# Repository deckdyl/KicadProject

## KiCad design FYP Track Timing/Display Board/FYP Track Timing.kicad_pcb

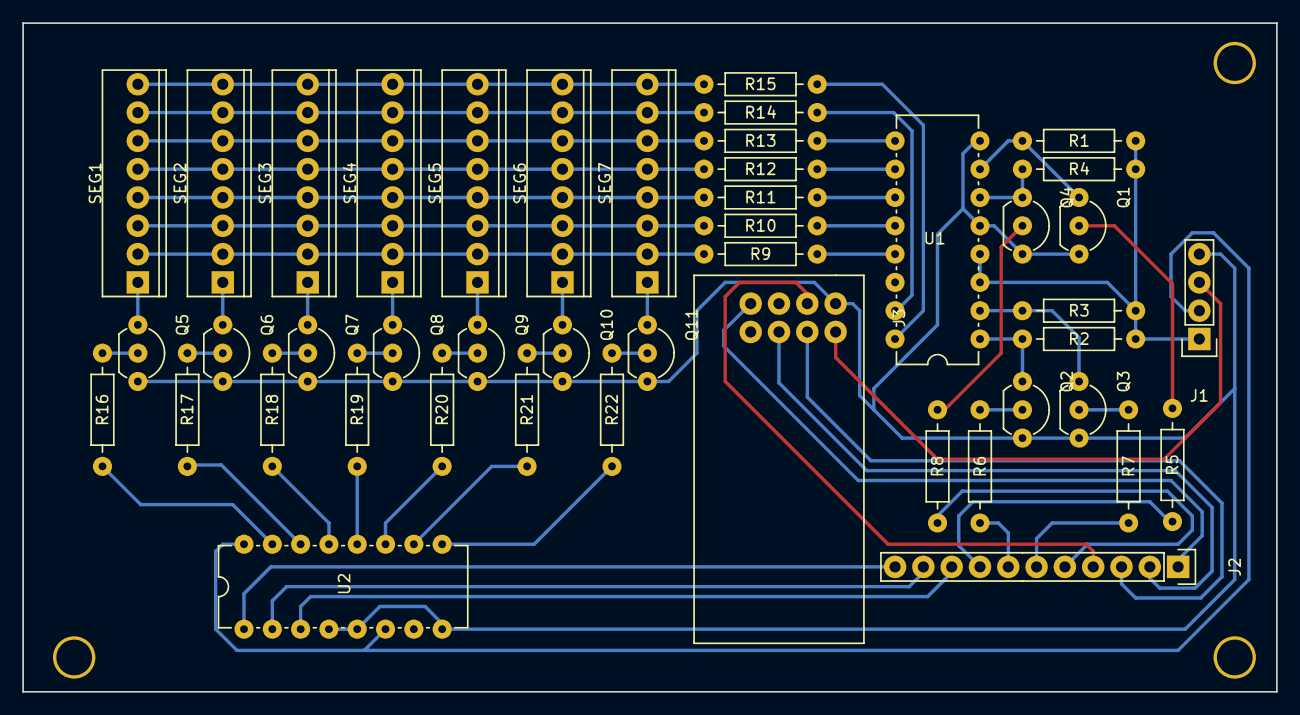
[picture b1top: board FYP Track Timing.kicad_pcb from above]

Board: 2 copper layers, 112.5 x 60.0 mm, 45 parts (0 on the bottom side), 58 nets.

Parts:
J1: Power; Pin_Header_Straight_1x04
J2: I/O; Pin_Header_Straight_1x11
J3: NRF24L01
Q1, Q2, Q3, Q4, Q5, Q6, Q7, Q8, Q9, Q10, Q11: 2N3904; TO-92_Inline_Wide
R1, R2, R3, R4: 10kΩ; Resistor-0.25W
R5, R6, R7, R8: 1kΩ; Resistor-0.25W
R9, R10, R11, R12, R13, R14, R15: 180Ω; Resistor-0.25W
R16, R17, R18, R19, R20, R21, R22: 470Ω; Resistor-0.25W
SEG1, SEG2, SEG3, SEG4, SEG5, SEG6, SEG7: KYX-30101AS; MolexHeader-7seg
U1: 4511; IC_PDIP_16pin
U2: 74HC238; IC_PDIP_16pin

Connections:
+3V3: J1.3, J3.2
+5V: J1.2, U2.6, U2.16
+9V: J1.1, R1.1, R2.1, R3.1, R4.1, U1.3, U1.4
GND: J1.4, J3.1, Q1.3, Q2.3, Q3.3, Q4.3, Q5.3, Q6.3, Q7.3, Q8.3, Q9.3, Q10.3, Q11.3, U1.5, U1.8, U2.4, U2.5, U2.8
unnamed: Q1.1, R1.2, U1.7
unnamed: Q1.2, R5.2
unnamed: Q2.1, R2.2, U1.1
unnamed: Q2.2, R6.2
unnamed: Q3.1, R3.2, U1.2
unnamed: Q3.2, R7.2
unnamed: Q4.1, R4.2, U1.6
unnamed: Q4.2, R8.2
unnamed: Q5.1, SEG1.1,5
unnamed: Q5.2, R16.2
unnamed: Q6.1, SEG2.1,5
unnamed: Q6.2, R17.2
unnamed: Q7.1, SEG3.1,5
unnamed: Q7.2, R18.2
unnamed: Q8.1, SEG4.1,5
unnamed: Q8.2, R19.2
unnamed: Q9.1, SEG5.1,5
unnamed: Q9.2, R20.2
unnamed: Q10.1, SEG6.1,5
unnamed: Q10.2, R21.2
unnamed: Q11.1, SEG7.1,5
unnamed: Q11.2, R22.2
unnamed: R9.1, U1.13
unnamed: R9.2, SEG1.7, SEG2.7, SEG3.7, SEG4.7, SEG5.7, SEG6.7, SEG7.7
unnamed: R10.1, U1.12
unnamed: R10.2, SEG1.6, SEG2.6, SEG3.6, SEG4.6, SEG5.6, SEG6.6, SEG7.6
unnamed: R11.1, U1.11
unnamed: R11.2, SEG1.4, SEG2.4, SEG3.4, SEG4.4, SEG5.4, SEG6.4, SEG7.4
unnamed: R12.1, U1.10
unnamed: R12.2, SEG1.3, SEG2.3, SEG3.3, SEG4.3, SEG5.3, SEG6.3, SEG7.3
unnamed: R13.1, U1.9
unnamed: R13.2, SEG1.2, SEG2.2, SEG3.2, SEG4.2, SEG5.2, SEG6.2, SEG7.2
unnamed: R14.1, U1.15
unnamed: R14.2, SEG1.9, SEG2.9, SEG3.9, SEG4.9, SEG5.9, SEG6.9, SEG7.9
unnamed: R15.1, U1.16
unnamed: R15.2, SEG1.10, SEG2.10, SEG3.10, SEG4.10, SEG5.10, SEG6.10, SEG7.10
unnamed: R16.1, U2.15
unnamed: R17.1, U2.14
unnamed: R18.1, U2.13
unnamed: R19.1, U2.12
unnamed: R20.1, U2.11
unnamed: R21.1, U2.10
unnamed: R22.1, U2.9
PinD2: J2.11, U2.1
PinD3: J2.10, U2.2
PinD4: J2.9, U2.3
PinD5: J2.8, R5.1
PinD6: J2.7, R6.1
PinD7: J2.6, R7.1
PinD8: J2.5, R8.1
PinD9: J2.4, J3.3
PinD10: J2.3, J3.4
PinD11: J2.2, J3.6
PinD12: J2.1, J3.7

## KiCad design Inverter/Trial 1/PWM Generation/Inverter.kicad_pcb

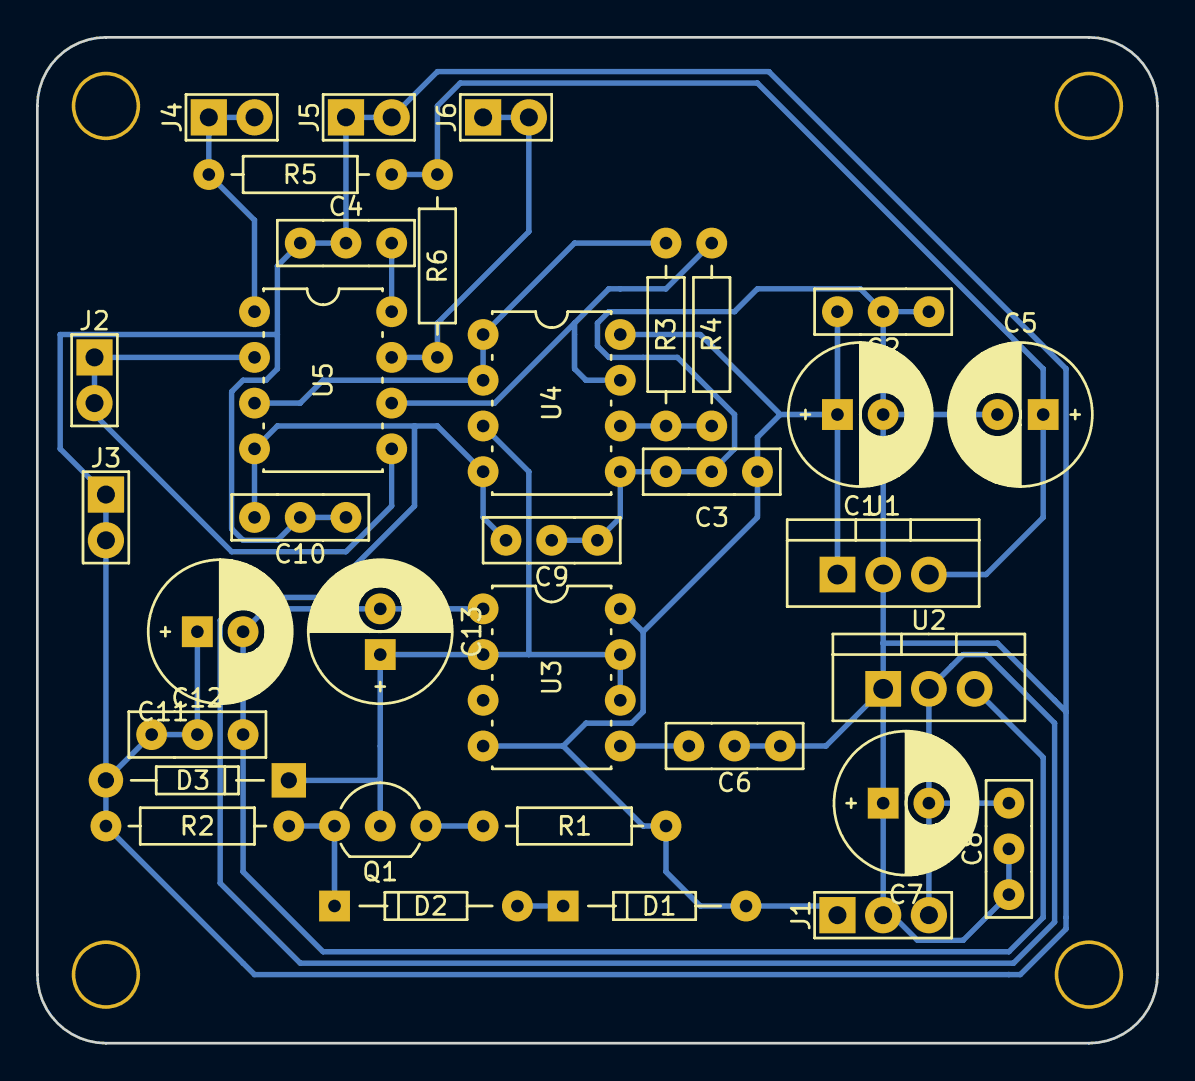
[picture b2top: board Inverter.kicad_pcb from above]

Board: 2 copper layers, 62.2 x 55.9 mm, 34 parts (0 on the bottom side), 15 nets.

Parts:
C1, C5, C7, C11: 33uF; Cap_Pol_Radial_D8_P2
C2, C3, C4, C6, C8, C9, C10, C12: 100nF; Cap_UnPol_P3
C13: 1uF; Cap_Pol_Radial_D8_P2
D1, D2: 1N4148
D3: 1N5818
J1: PWR; Pin_Header_Straight_1x03
J2: Sine Input; Pin_Header_Straight_1x02
J3, J5: GND; Pin_Header_Straight_1x02
J4: P-Half-PWM; Pin_Header_Straight_1x02
J6: N-Half-PWM; Pin_Header_Straight_1x02
Q1: 2N3906; TO-92_Inline_Wide
R1: 56Ω; Resistor-0.25W
R2, R5, R6: 1.2kΩ; Resistor-0.25W
R3, R4: 10kΩ; Resistor-0.25W
U1: 7805; 78XX-V.Regulator
U2: 7905; 79XX-V.Regulator
U3: NE555; IC_PDIP_8pin
U4: LM358; IC_PDIP_8pin
U5: LM393; IC_PDIP_8pin

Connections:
+5V: C5.1, C6.1, R5.2, R6.2, U1.VO, U3.5
+8V: C1.1, C2.1, C3.1, C4.1, D1.2, J1.1, R1.1, U1.VI, U3.4, U3.8, U4.8, U5.8
-5V: C11.2, C12.1, C13.2, U2.VO, U3.1
-8V: C7.2, C8.1, C9.1, C10.1, J1.3, U2.VI, U4.4, U5.4
GND: C1.2, C2.2, C3.2, C4.2, C5.2, C6.2, C7.1, C8.2, C9.2, C10.2, C11.1, C12.2, D3.2, J1.2, J3.1, J3.2, J5.1, J5.2, R2.1, U1.GND, U2.GND, U4.5
unnamed: D1.1, D2.2
unnamed: D2.1, Q1.1, R2.2
unnamed: J4.1, J4.2, R5.1, U5.1
unnamed: J6.1, J6.2, R6.1, U5.7
unnamed: Q1.3, R1.2
unnamed: R3.1, R4.2, U4.6
SawtoothBuffered: R3.2, U4.1, U4.2, U5.3
SawtoothInverted: R4.1, U4.7, U5.6
SawtoothWave: C13.1, D3.1, Q1.2, U3.2, U3.6, U3.7, U4.3
SineWave: J2.1, J2.2, U5.2, U5.5

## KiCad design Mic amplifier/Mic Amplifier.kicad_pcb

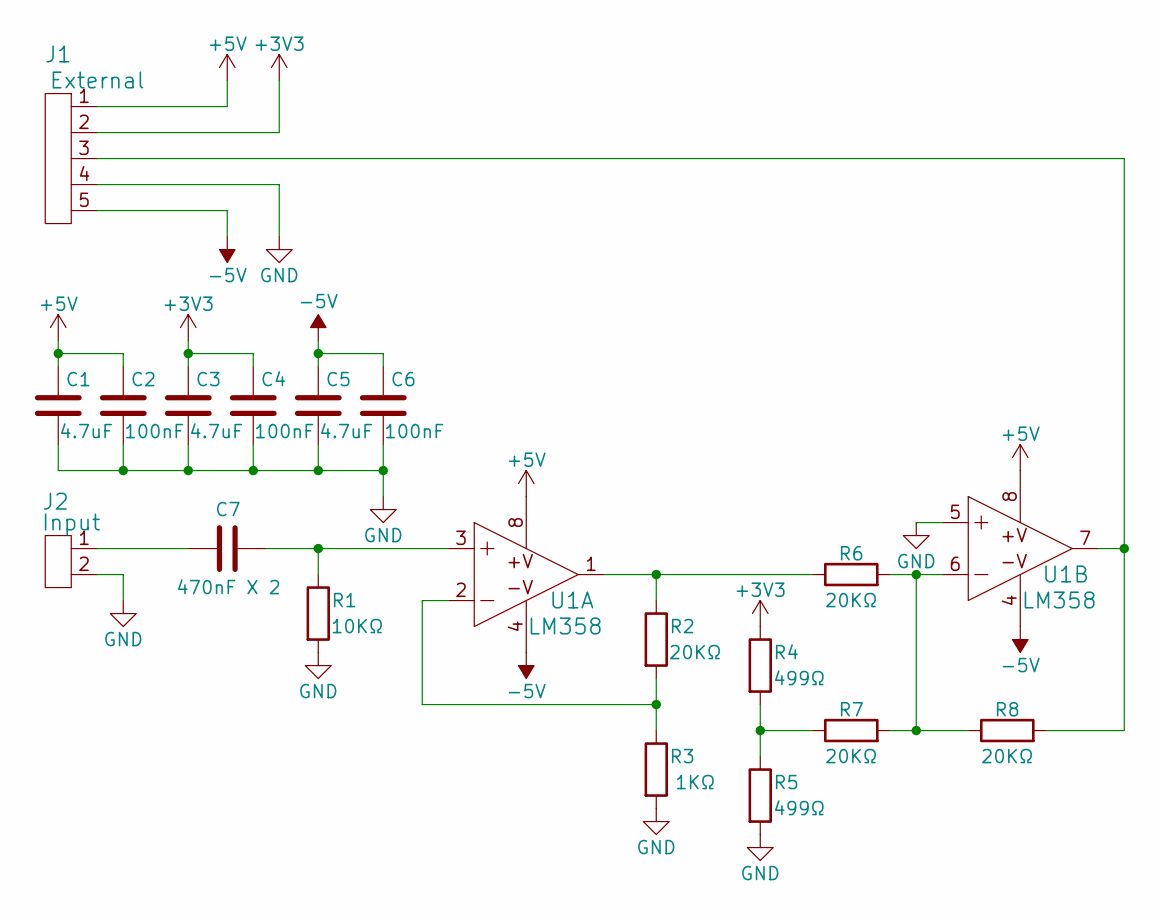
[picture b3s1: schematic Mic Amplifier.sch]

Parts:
C1, C3, C5: 4.7uF; C_0603_HandSoldering
C2, C4, C6: 100nF; C_0603_HandSoldering
C7: 470nF X 2; Capacitor_SMD_2824
J1: External; Pin_Header_Straight_1x05
J2: Input; Pin_Header_Straight_1x02
R1: 10KΩ; R_0603_HandSoldering
R2, R6, R7, R8: 20KΩ; R_0603_HandSoldering
R3: 1KΩ; R_0603_HandSoldering
R4, R5: 499Ω; R_0603_HandSoldering
U1: LM358; IC_PDIP_8pin

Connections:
+3V3: C3.1, C4.1, J1.2, R4.1
+5V: C1.1, C2.1, J1.1, U1.8
-5V: C5.1, C6.1, J1.5, U1.4
GND: C1.2, C2.2, C3.2, C4.2, C5.2, C6.2, J1.4, J2.2, R1.2, R3.2, R5.2, U1.5
unnamed: C7.1, R1.1, U1.3
unnamed: C7.2, J2.1
unnamed: J1.3, R8.2, U1.7
unnamed: R2.1, R6.1, U1.1
unnamed: R2.2, R3.1, U1.2
unnamed: R4.2, R5.1, R7.1
unnamed: R6.2, R7.2, R8.1, U1.6

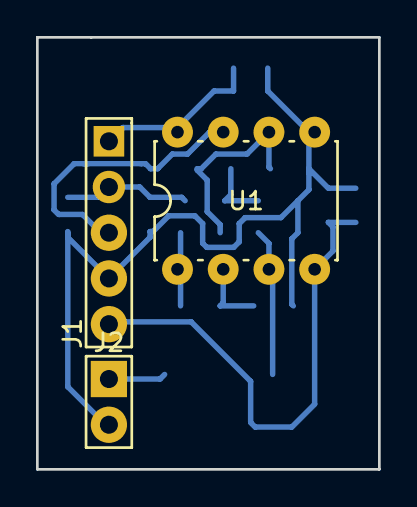
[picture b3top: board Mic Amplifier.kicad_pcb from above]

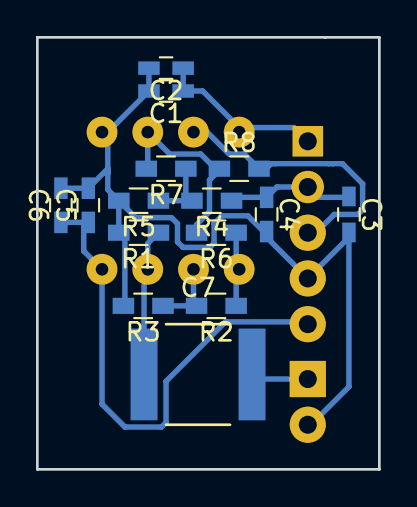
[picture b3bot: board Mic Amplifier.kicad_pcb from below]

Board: 2 copper layers, 19.0 x 24.0 mm, 18 parts (15 on the bottom side), 11 nets.

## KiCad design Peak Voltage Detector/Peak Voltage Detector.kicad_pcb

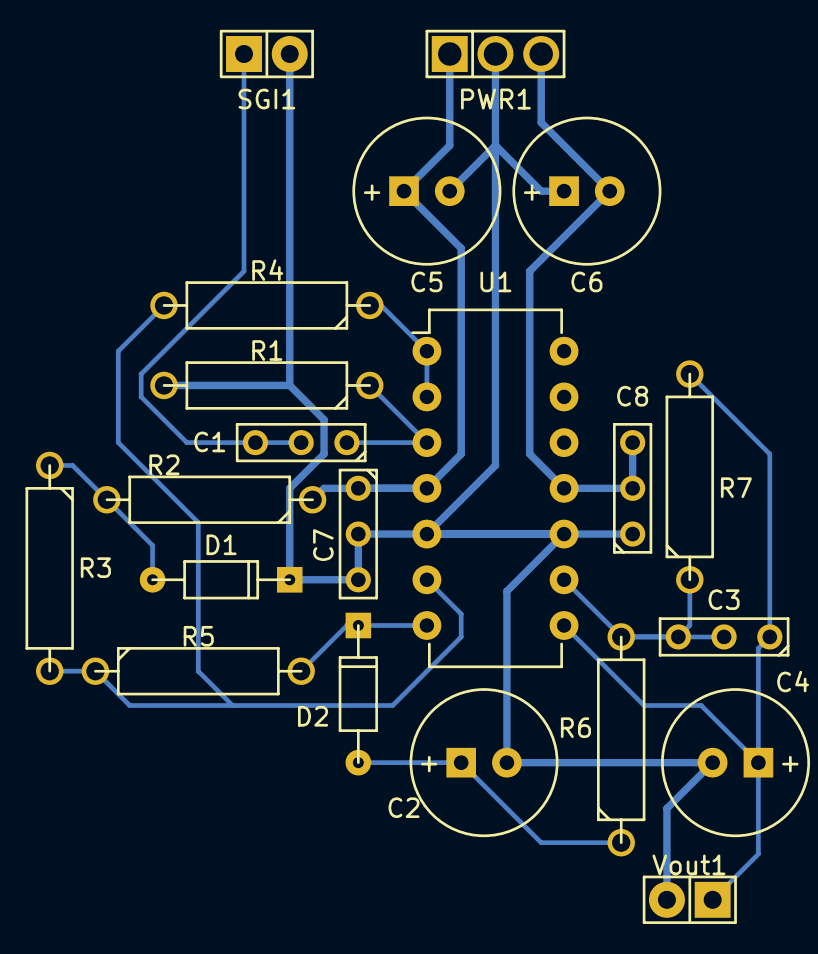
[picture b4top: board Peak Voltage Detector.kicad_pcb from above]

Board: 2 copper layers, 21 parts (0 on the bottom side), 12 nets.

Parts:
C1, C7, C8: 100nF; C1-1
C2: 3.3uF; C1V8
C3: 68nF; C1-1
C4: 1.5uF; C1V8
C5, C6: 10uF; C1V8
D1, D2: 1N914; DO-35
PWR1: Header 1X3; PIN_ARRAY_3X1
R1: 47kΩ; R4-5
R2, R3, R4, R5: 10kΩ; R4-5
R6, R7: 100kΩ; R4-5
SGI1: Header 1X2; PIN_ARRAY_2X1
U1: TL084; DIP-14_W7.62mm
Vout1: Header 1X2; PIN_ARRAY_2X1

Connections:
+12V: C5.1, C7.1, PWR1.1, R2.1, U1.4
-12V: C6.2, C8.2, PWR1.3, U1.11
GND: C2.2, C4.2, C5.2, C6.1, C7.2, C8.1, D1.1, PWR1.2, R1.2, SGI1.2, U1.5, U1.10, Vout1.2
unnamed: C1.1, R1.1, U1.3
unnamed: C1.2, SGI1.1
unnamed: C2.1, D2.2, R6.1
unnamed: C3.1, C4.1, R7.2, U1.8, Vout1.1
unnamed: C3.2, R6.2, R7.1, U1.9
unnamed: D1.2, R2.2, R3.1
unnamed: D2.1, R5.2, U1.7
unnamed: R3.2, R4.2, R5.1, U1.6
unnamed: R4.1, U1.1, U1.2

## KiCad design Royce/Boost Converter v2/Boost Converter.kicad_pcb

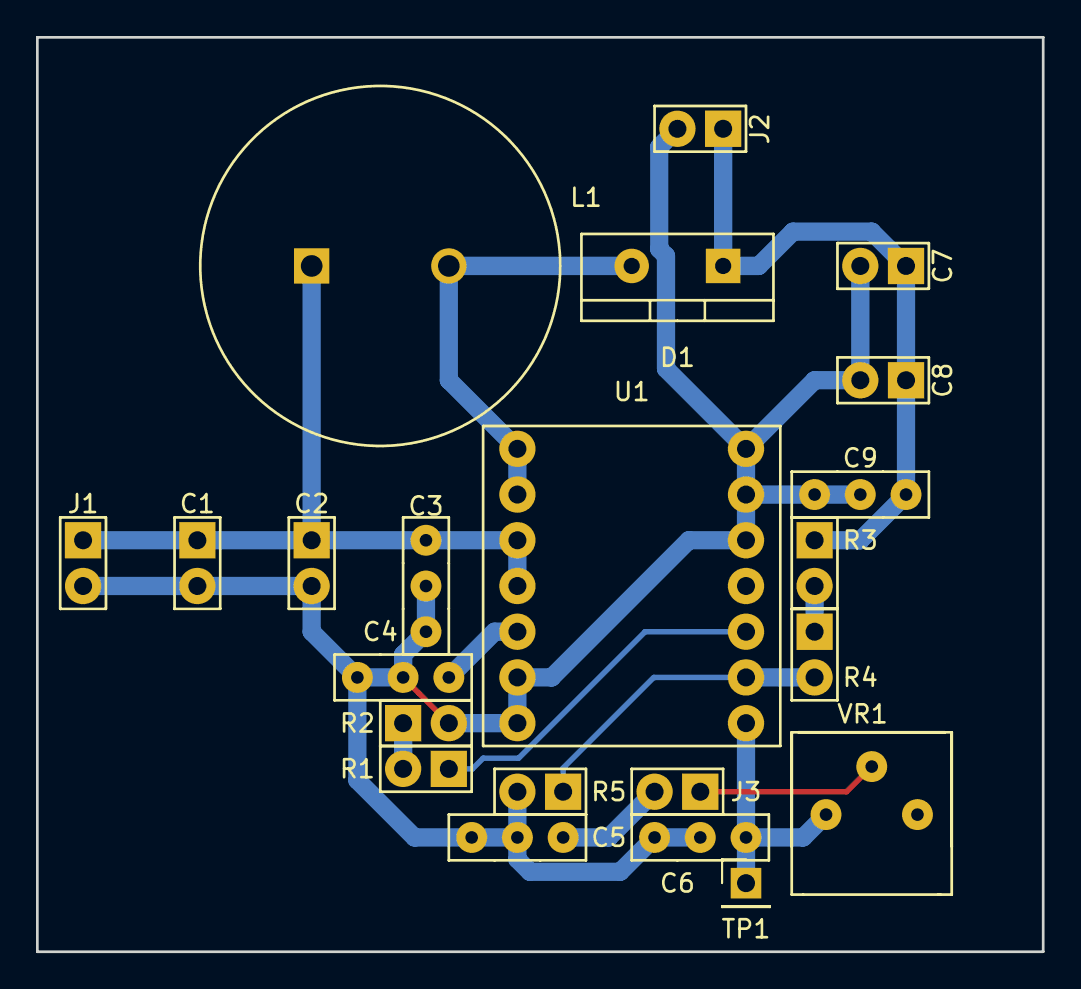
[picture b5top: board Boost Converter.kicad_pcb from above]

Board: 2 copper layers, 55.9 x 50.8 mm, 22 parts (0 on the bottom side), 12 nets.

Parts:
C1, C2, C7, C8: 22uF; Pin_Header_Straight_1x02
C3, C5, C9: 100nF; Cap_UnPol_P3
C4: 22n; Cap_UnPol_P3
C6: 270pF; Cap_UnPol_P3
D1: MBR790; TO-220_Neutral12_Vertical
J1: Input; Pin_Header_Straight_1x02
J2: Output; Pin_Header_Straight_1x02
J3: Jumper; Pin_Header_Straight_1x02
L1: 22uH; Inductor-22uH-5.4A
R1: 120kΩ; Pin_Header_Straight_1x02
R2: 6.6kΩ; Pin_Header_Straight_1x02
R3, R4: 91kΩ; Pin_Header_Straight_1x02
R5: 10kΩ; Pin_Header_Straight_1x02
TP1: TestPoint; Pin_Header_Straight_1x01_Pitch2.54mm
U1: TPS55340; Adapter-14Pin
VR1: 5kΩ; Potentiometer_Bourns_3386

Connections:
GND: C1.2, C2.2, C3.2, C4.2, C5.2, C6.2, C7.2, C8.2, C9.2, J1.2, J2.2, R2.2, R5.2, U1.6, U1.7, U1.12, U1.13, U1.14
unnamed: C1.1, C2.1, C3.1, J1.1, L1.1, U1.3, U1.4
unnamed: C4.1, U1.5
unnamed: C5.1, J3.2
unnamed: C6.1, TP1.1, U1.8, VR1.1
unnamed: C7.1, C8.1, C9.1, D1.1, J2.1, R3.1
unnamed: D1.2, L1.2, U1.1, U1.2
unnamed: J3.1, VR1.2
unnamed: R1.1, U1.10
unnamed: R1.2, R2.1
unnamed: R3.2, R4.1
unnamed: R4.2, R5.1, U1.9

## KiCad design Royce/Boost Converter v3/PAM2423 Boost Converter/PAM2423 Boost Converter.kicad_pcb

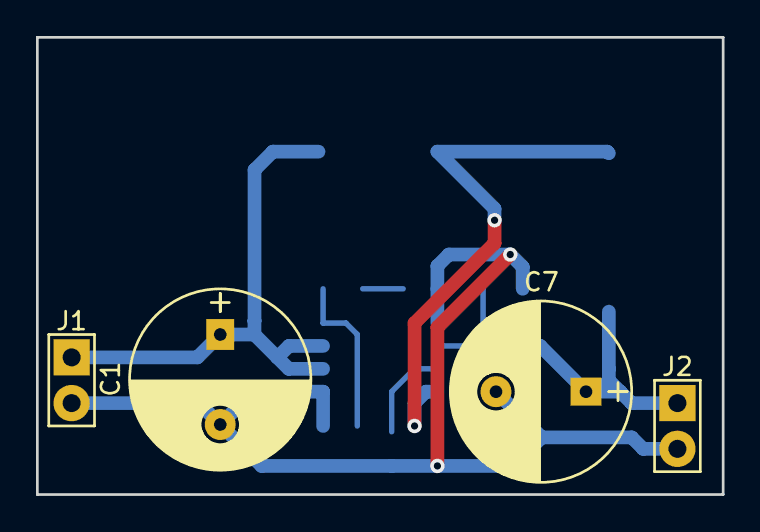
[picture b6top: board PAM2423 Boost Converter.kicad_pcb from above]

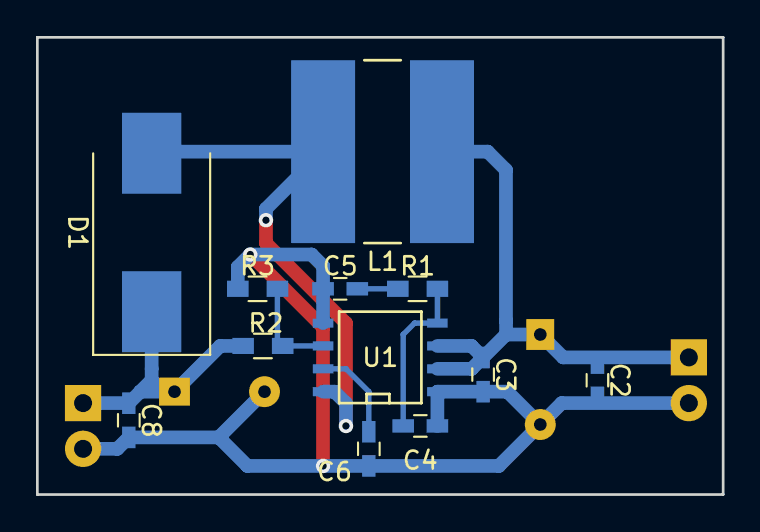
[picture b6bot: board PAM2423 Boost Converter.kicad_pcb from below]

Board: 2 copper layers, 38.1 x 25.4 mm, 16 parts (12 on the bottom side), 8 nets.

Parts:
C1, C7: 100uF; Cap_Pol_Radial_D10_P3
C2, C8: 10uF; C_0603_HandSoldering
C3: 1uF; C_0603_HandSoldering
C4: 47pF; C_0603_HandSoldering
C5: 2.2nF; C_0603_HandSoldering
C6: 10nF; C_0603_HandSoldering
D1: B330; D_SMC_Handsoldering
J1: Input; Pin_Header_Straight_1x02
J2: Output; Pin_Header_Straight_1x02
L1: 6.8uH; Inductor_SMD-9.8X10
R1: 51kΩ; R_0603_HandSoldering
R2: 86.6kΩ; R_0603_HandSoldering
R3: 10kΩ; R_0603_HandSoldering
U1: PAM2423; SOIC-8-N

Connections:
GND: C1.2, C2.2, C3.2, C4.2, C5.2, C6.2, C7.2, C8.2, J1.2, J2.2, R3.2, U1.1, U1.5
unnamed: C1.1, C2.1, C3.1, J1.1, L1.1, U1.2, U1.3
unnamed: C4.1, R1.1, U1.4
unnamed: C5.1, R1.2
unnamed: C6.1, U1.7
unnamed: C7.1, C8.1, D1.1, J2.1, R2.1
unnamed: D1.2, L1.2, U1.8
unnamed: R2.2, R3.1, U1.6
